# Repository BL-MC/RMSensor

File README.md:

# RM Sensor
31mm Diameter board using SMD 0805_2012 footprints for resistors and capacitors  
## Schematic

## PCB with no fill

## PCB with fill

## PCB with front fill

## PCB with back fill

## 3D View of the front of the PCB

## 3D View of the back of the PCB

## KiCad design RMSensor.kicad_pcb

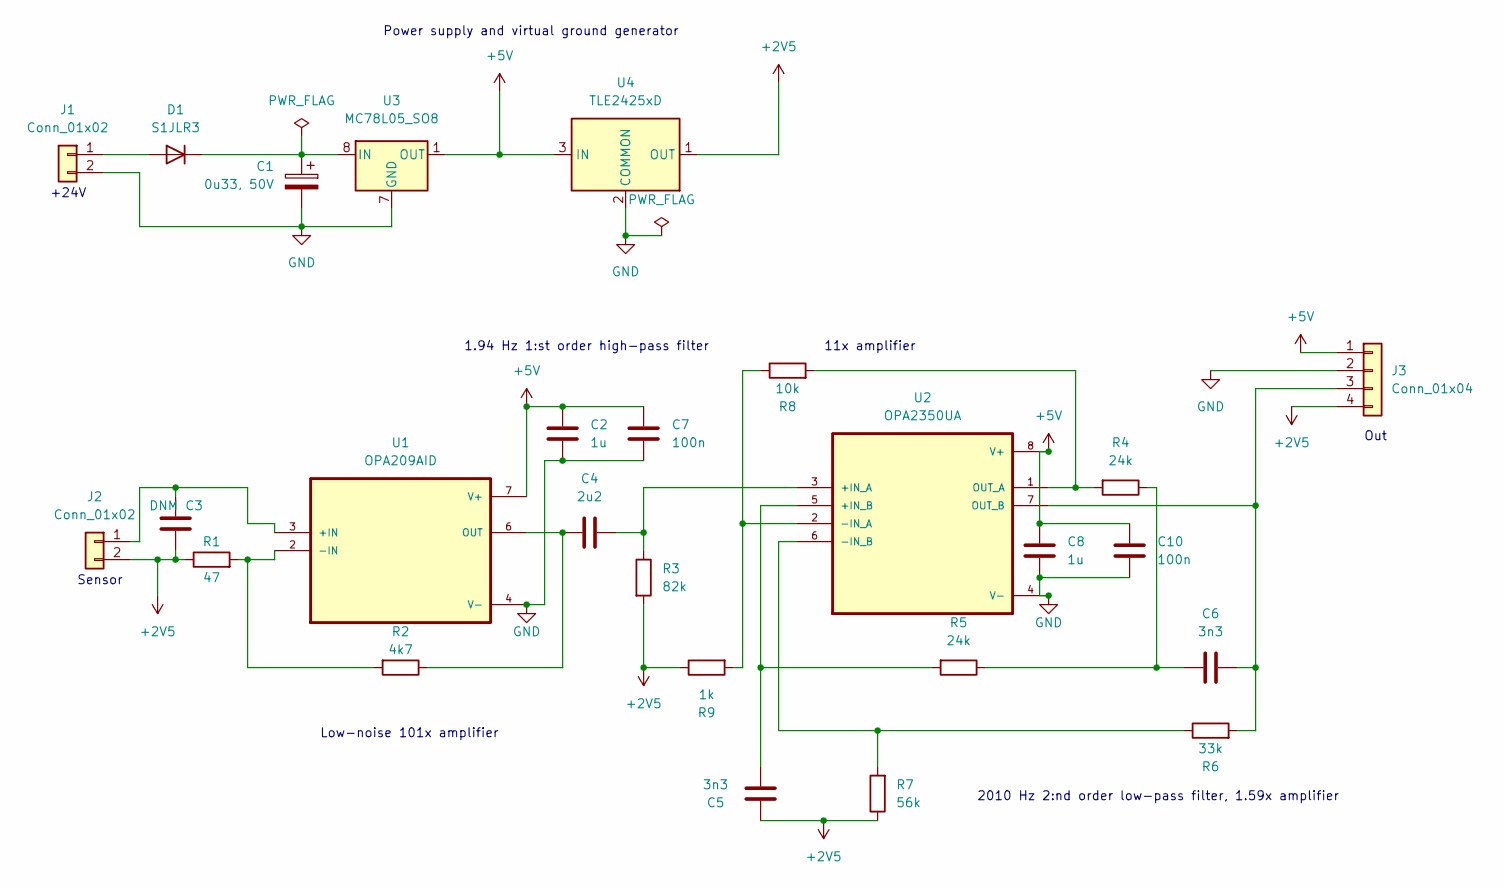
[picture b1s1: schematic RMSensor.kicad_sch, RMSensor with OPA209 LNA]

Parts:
C1: 0u33, 50V; C_0805_2012Metric
C2, C8: 1u; C_0805_2012Metric
C3: DNM; C_0805_2012Metric
C4: 2u2; C_0805_2012Metric
C5, C6: 3n3; C_0805_2012Metric
C7, C10: 100n; C_0805_2012Metric
D1: S1JLR3; Sub-sma
J1, J2: Conn_01x02; TwoHoleConnector
J3: Conn_01x04; FourHoleConnector
R1: 47; R_0805_2012Metric
R2: 4k7; R_0805_2012Metric
R3: 82k; R_0805_2012Metric
R4, R5: 24k; R_0805_2012Metric
R6: 33k; R_0805_2012Metric
R7: 56k; R_0805_2012Metric
R8: 10k; R_0805_2012Metric
R9: 1k; R_0805_2012Metric
U1: OPA209AID; SOIC127P599X175-8N
U2: OPA2350UA; SOIC127P599X175-8N
U3: MC78L05_SO8; SOIC-8_3.9x4.9mm_P1.27mm
U4: TLE2425xD; SOIC-8_3.9x4.9mm_P1.27mm

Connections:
+2V5: C3.2, C5.2, J2.2, J3.4, R1.1, R3.2, R7.1, R9.1, U4.1 (OUT)
+5V: C2.1, C7.1, C8.1, C10.1, J3.1, U1.7 (V+), U2.8 (V+), U3.1 (OUT), U4.3 (IN)
GND: C1.2, C2.2, C7.2, C8.2, C10.2, J1.2, J3.2, U1.4 (V-), U2.4 (V-), U3.2 (GND), U3.3 (GND), U3.6 (GND), U3.7 (GND), U4.2 (COMMON)
unnamed: C1.1, D1.1 (K), U3.8 (IN)
unnamed: C3.1, J2.1, U1.3 (+IN)
unnamed: C4.1, R3.1, U2.3 (+IN_A)
unnamed: C4.2, R2.1, U1.6 (OUT)
unnamed: C5.1, R5.2, U2.5 (+IN_B)
unnamed: C6.1, R4.1, R5.1
unnamed: C6.2, J3.3, R6.2, U2.7 (OUT_B)
unnamed: D1.2 (A), J1.1
unnamed: R1.2, R2.2, U1.2 (-IN)
unnamed: R4.2, R8.2, U2.1 (OUT_A)
unnamed: R6.1, R7.2, U2.6 (-IN_B)
unnamed: R8.1, R9.2, U2.2 (-IN_A)

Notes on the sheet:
11x amplifier
Sensor
Out
+24V
2010 Hz 2:nd order low-pass filter, 1.59x amplifier
1.94 Hz 1:st order high-pass filter
Power supply and virtual ground generator
Low-noise 101x amplifier

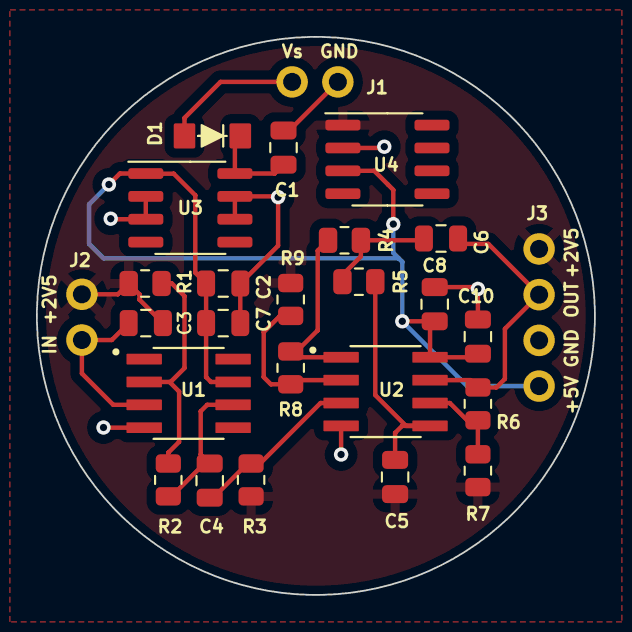
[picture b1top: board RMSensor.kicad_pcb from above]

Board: 2 copper layers, 31.0 x 31.0 mm, 26 parts (0 on the bottom side), 15 nets.

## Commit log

2023-02-19 first commit working schematic
2023-02-19 updated README with images
2023-02-27 changed res and cap footprint to 805 and changed regulator
2023-03-01 pcb with traces
2023-03-03 31mm board
